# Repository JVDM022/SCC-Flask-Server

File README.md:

# scc-control-platform

A small SCADA-like research control platform for a thermal SCC/corrosion test rig. Arduino SCC firmware owns rig safety and fallback control, while an Intel NUC USB gateway handles communications to the Flask backend. PostgreSQL stores the time series, and the backend derives alarms, pump-cycle statistics, ML temperature predictions, and guarded MPC heater PWM recommendations. The React HMI dashboard provides live monitoring, trends, alarms, events, ML predictions, MPC output, firmware updates, and equipment health views.

## Architecture

```text
Arduino SCC controller -> USB serial -> Intel NUC gateway -> Flask API -> PostgreSQL
                                                                  |-> alarms and events
                                                                  |-> pump-cycle extraction
                                                                  |-> ML prediction
                                                                  |-> guarded MPC (opt-in)
                                                                  |-> React HMI dashboard
```

## Docker Setup

```bash
docker compose up --build
```

Backend: `http://localhost:5050`  
Frontend: `http://localhost:5173`

## Frontend HMI

The HMI is a React + Vite + TypeScript app in `frontend/hmi-dashboard`. It uses React Query for API polling, Plotly for dark engineering charts, and modular dashboard pages for operations, analytics, ML models, MPC, digital twin simulation, equipment health, event intelligence, and settings.

```bash
cd frontend/hmi-dashboard
npm install
npm run dev
```

## Live Telemetry

The default live path reads Arduino CSV telemetry over USB on the Intel NUC and posts parsed JSON to Flask:

```bash
cd backend
python -m app.services.nuc_gateway --serial-port /dev/ttyACM0 --api-base-url http://localhost:5000
```

Set `API_WRITE_KEY` in both the backend and gateway environment when write authentication is enabled. Common NUC gateway variables:

```text
NUC_SERIAL_PORT=/dev/ttyACM0
NUC_SERIAL_BAUD=115200
SCC_API_BASE_URL=http://localhost:5000
NUC_DEVICE_ID=intel-nuc-gateway
NUC_AVRDUDE_COMMAND=avrdude
NUC_ARDUINO_UPLOAD_BAUD=115200
```

Legacy ESP32 relay telemetry is still supported through MQTT. Devices publish JSON to:

```text
scc/site/<site_id>/rig/<rig_id>/device/<device_id>/telemetry
```

The Flask backend subscribes to Mosquitto when `MQTT_ENABLED=1`, parses MQTT payloads, stores telemetry, and derives alarms, pump-cycle records, ML predictions, and MPC recommendations.

## API Endpoints

- `GET /api/latest`: latest telemetry row.
- `GET /api/history?minutes=60`: telemetry history for plotting.
- `GET /api/events?limit=100`: pump and hard-kill events.
- `GET /api/alarms/active`: active alarms.
- `GET /api/pump-cycles`: extracted pump cycle statistics.
- `GET /api/ml/prediction`: predicted temperatures for +1s, +5s, and +10s when models exist.
- `GET /api/mpc/status`: closed-loop enablement, model horizons, watchdog, and latest command state.
- `GET /api/mpc/recommendation`: advisory heater PWM recommendation.
- `POST /api/control/setpoint`: store a desired setpoint command.
- `POST /api/control/power`: queue a controller on/off command through the Intel NUC gateway.
- `POST /api/telemetry`: JSON telemetry ingest used by the Intel NUC gateway and development tools.
- `POST /api/telemetry/csv`: development/manual CSV import, not the live ESP32 path.

## Telemetry Format

Live MQTT telemetry is JSON. The development CSV import endpoint accepts CSV with or without a header. Headerless rows are parsed using this exact order:

```text
event,ms,temp_c,adc,dtemp_c_per_s,setpoint_c,mode,heater_pwm,heating,heater_lockout,pump_enabled,pump_allowed,pump_on,motor_pwm,motor_on_ms,motor_period_ms,temp_before_pump_c,min_temp_after_pump_c,last_pump_drop_c,recovery_time_s,manual_kill,hard_kill,uptime_s
```

Example:

```text
0,123456,126.42,222,-0.1300,125.00,3,184,1,0,1,1,0,155,150,30000,127.20,124.80,2.40,18.50,0,0,300
```

Event codes: `0` normal sample, `1` pump start, `2` pump end, `3` pump recovered, `4` hard kill, `5` sensor fault.

## Safety Philosophy

Arduino firmware and hardware own hard safety. Flask, ML, MPC, and the Intel NUC gateway are never the only protection layer. Closed-loop MPC is disabled by default (`MPC_CLOSED_LOOP_ENABLED=0`). When enabled, it only sends PWM overrides in PID-hold mode with ten contiguous telemetry samples and a loaded 5-second model. The Arduino expires an override after 3.5 seconds and returns to local PID. Heater lockout, a target-plus-0.5 C ceiling, manual kill, sensor fault, the optional runtime limit, and hard kill remain local firmware overrides.

The continuous-operation build sets `ENABLE_RUNTIME_LIMIT=0`, so it does not force a shutdown after 96 hours. Set the flag to `1` to restore that behavior. Manual kill, ADC/thermistor fault detection, heater lockout, and the hard temperature kill remain active regardless of this setting. Arduino `millis()` telemetry wraps normally after approximately 49.7 days.

The trained model is observational, so the backend also enforces a physically directed recovery floor: at least PWM 184 when temperature is 2 C or more below setpoint, and at least PWM 128 when it is 0.5 C or more below setpoint. This prevents a reverse-causality artifact in the training data from selecting zero heat during recovery.

Before each pump cycle, the backend also probes the 5-second model with a simulated pump-start state. It combines the predicted drop with the last measured pump drop and calculates `preheat target = setpoint + drop`, capped by `MPC_PREHEAT_MAX_C`. The Arduino waits for this target before re-enabling the pump. Its compile-time `MPC_PREHEAT_LIMIT_Cx100`, lockout, and hard-kill thresholds remain independent limits; changing the validated safety envelope requires reviewing all of them together.

## Manual Emergency Control

The Arduino starts in a fail-safe OFF state. The Operations HMI queues `SET_ON 1` to enable both heater control and the pump timer, and `SET_ON 0` to turn both outputs off. `KILL 1` immediately latches the system OFF; after `KILL 0`, the operator must deliberately select Turn On again. Set `API_WRITE_KEY` on the backend and `VITE_API_WRITE_KEY` on the frontend to the same value when command authentication is enabled. The NUC gateway polls:

```text
/api/firmware/commands/next?device=nuc
```

Pending manual kill and setpoint commands are delivered through that endpoint before Arduino OTA commands. Existing ESP32 relay firmware can still poll with `device=esp32` for legacy deployments.

## Dependency Explanation

- Flask: API server
- SQLAlchemy: ORM
- PostgreSQL: database
- pandas/numpy: data processing
- scikit-learn: ML models
- joblib: model persistence
- matplotlib/plotly: visualization
- APScheduler: background jobs
- pytest: testing
- xgboost/lightgbm: advanced ML models

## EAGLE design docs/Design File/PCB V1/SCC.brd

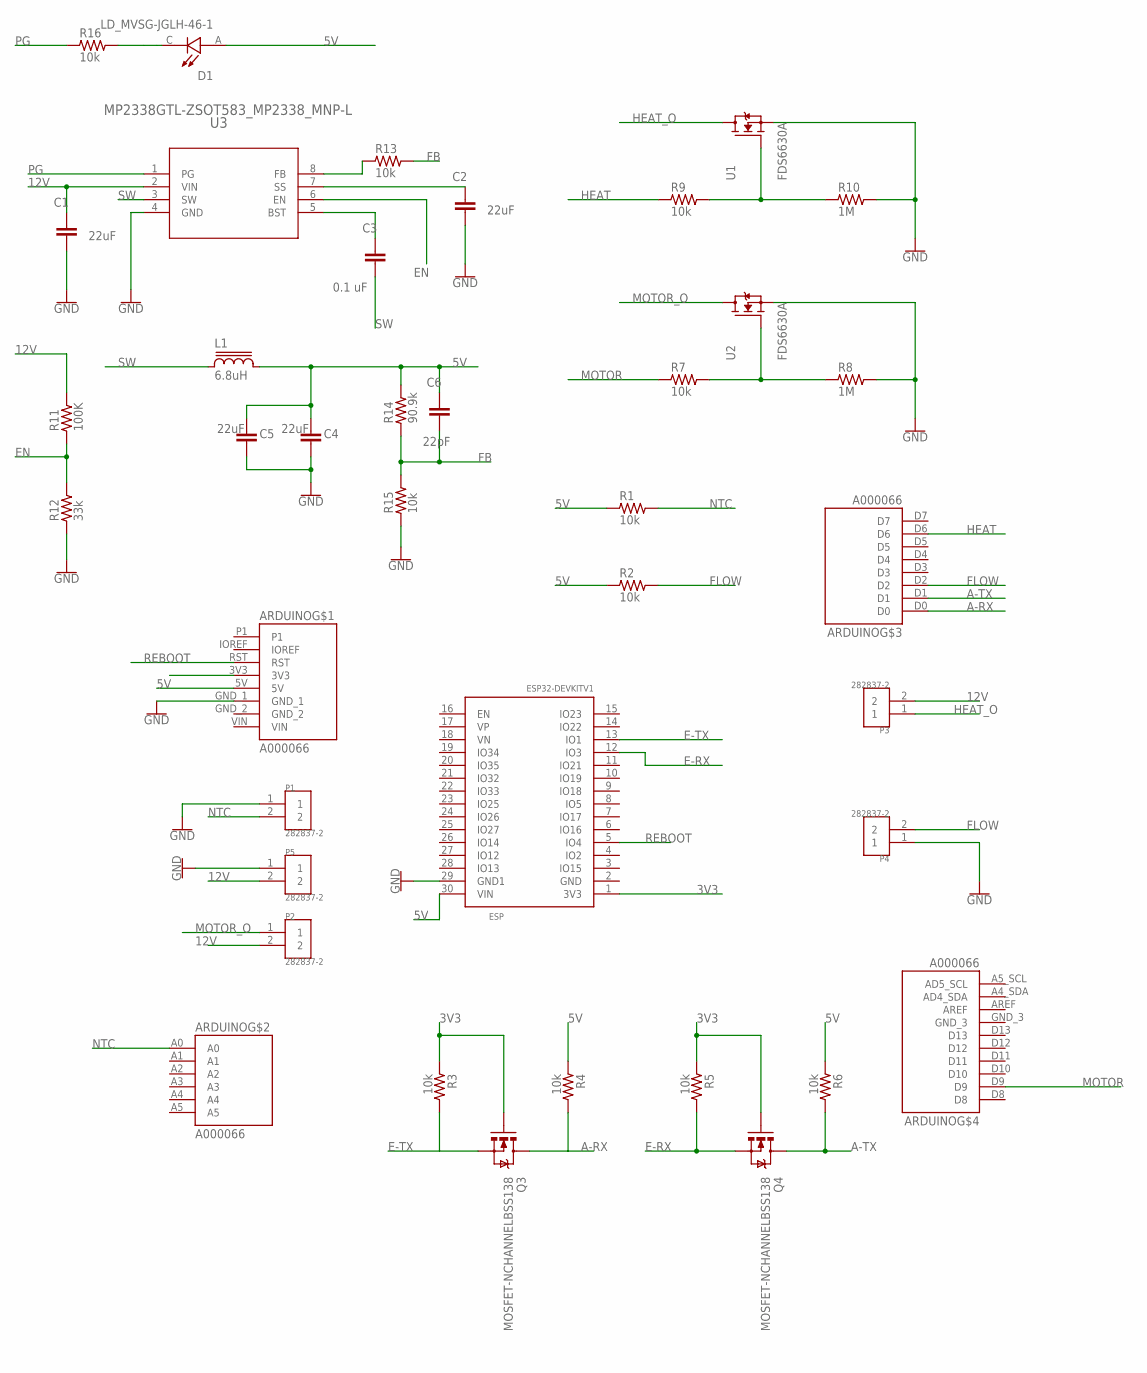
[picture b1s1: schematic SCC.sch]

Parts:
ARDUINO: A000066; ARDUINO_A000066
C1, C2, C4, C5: 22uF; CAP_1206
C3: 0.1 uF; CAP_0805
C6: 22pF; CAP_0805
D1: LD_MVSG-JGLH-46-1; LED_LD_MVSG-JGLH-46-1
ESP: ESP32DEVKITV1; ESP32-DEVKITV1
L1: 6.8uH; INDUCTOR-BOURNS_SRN8040
P1, P2, P3, P4, P5: 282837-2; TE_282837-2
Q3, Q4: MOSFET-NCHANNELBSS138; SOT23
R1, R2, R3, R4, R5, R6, R7, R9, R13, R15, R16: 10k; RC-MASTER-SMD_R0603MP
R8, R10: 1M; RC-MASTER-SMD_R0603MP
R11: 100K; RC-MASTER-SMD_R0603MP
R12: 33k; RC-MASTER-SMD_R0603MP
R14: 90.9k; RC-MASTER-SMD_R0603MP
U1, U2: FDS6630A; SOIC127P600X175-8N
U3: MP2338GTL-ZSOT583_MP2338_MNP-L; SOT583_MP2338_MNP-L

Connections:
3V3: ESP.1 (3V3), Q3.1 (G), Q4.1 (G), R3.1, R5.1
5V: ARDUINO.5V, C4.1, C5.1, C6.1, D1.A, ESP.30 (VIN), L1.2, R1.1, R2.1, R4.1, R6.1, R14.2
12V: C1.1, P2.2, P3.2, P5.2, R11.2, U3.2 (VIN)
A-RX: ARDUINO.D0, Q3.3 (D), R4.2
A-TX: ARDUINO.D1, Q4.3 (D), R6.2
E-RX: ESP.12 (IO3), Q4.2 (S), R5.2
E-TX: ESP.13 (IO1), Q3.2 (S), R3.2
EN: R11.1, R12.2, U3.6 (EN)
FB: C6.2, R13.2, R14.1, R15.2
FLOW: ARDUINO.D2, P4.2, R2.2
GND: ARDUINO.GND_1, C1.2, C2.2, C4.2, C5.2, ESP.29 (GND1), P1.1, P4.1, P5.1, R8.2, R10.2, R12.1, R15.1, U1.1 (S), U1.2 (S), U1.3 (S), U2.1 (S), U2.2 (S), U2.3 (S), U3.4 (GND)
GND_2: ARDUINO.GND_2
GND_3: ARDUINO.GND_3
HEAT: ARDUINO.D6, R9.1
HEAT_O: P3.1, U1.5 (D), U1.6 (D), U1.7 (D), U1.8 (D)
MOTOR: ARDUINO.D9, R7.1
MOTOR_O: P2.1, U2.5 (D), U2.6 (D), U2.7 (D), U2.8 (D)
unnamed: R7.2, R8.1, U2.4 (G)
unnamed: R9.2, R10.1, U1.4 (G)
unnamed: C3.1, U3.5 (BST)
unnamed: C2.1, U3.7 (SS)
unnamed: D1.C, R16.2
unnamed: R13.1, U3.8 (FB)
NTC: ARDUINO.A0, P1.2, R1.2
PG: R16.1, U3.1 (PG)
REBOOT: ARDUINO.RST, ESP.5 (IO4)
SW: C3.2, L1.1, U3.3 (SW)
VIN: ARDUINO.VIN

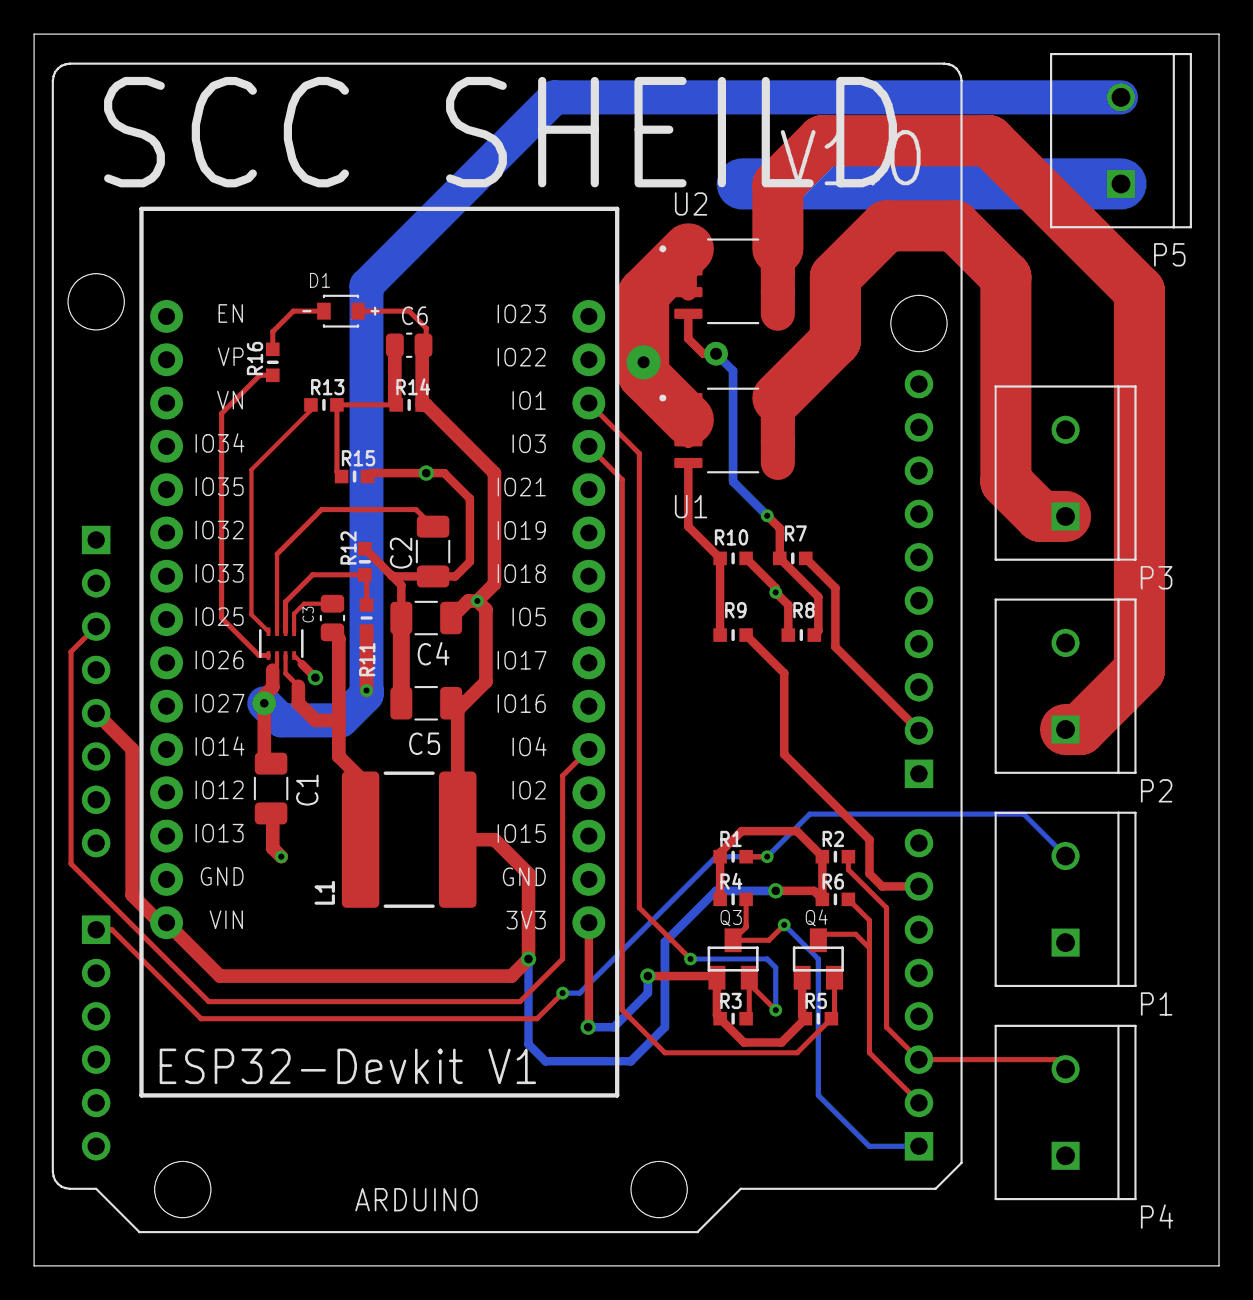
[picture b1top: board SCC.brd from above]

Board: 2 copper layers, 69.5 x 72.2 mm, 36 parts (0 on the bottom side), 25 nets.

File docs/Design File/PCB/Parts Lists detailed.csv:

"Part";"Value";"Device";"Package";"Description";"AVAILABILITY";"CHECK_PRICES";"COPYRIGHT";"CREATED_BY";"DATASHEET";"DESCRIPTION";"DIGIKEY_PART_NUMBER";"MANUFACTURER";"MANUFACTURER_NAME";"MANUFACTURER_PART_NUMBER";"MAXIMUM_PACKAGE_HEIGHT";"MF";"MP";"MPN";"PACKAGE";"PARTREV";"PRICE";"PROD_ID";"PURCHASE-URL";"SNAPEDA_LINK";"STANDARD";
"ARDUINO";"A000066";"A000066";"ARDUINO_A000066";"Check availability";"In Stock";"https://www.snapeda.com/parts/A000066/Arduino/view-part/?ref=eda";"";"";"";"                                                      Arduino UNO Rev3 Microcontroller Board, ATmega328P | Arduino A000066                                              ";"";"";"";"";"";"Arduino";"A000066";"";"Non-Standard Arduino";"";"None";"";"https://www.snapeda.com/api/url_track_click_mouser/?unipart_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 uno r3";"https://www.snapeda.com/parts/A000066/Arduino/view-part/?ref=snap";"";
"C1";"22uF";"GRM31CR60J107ME39L";"CAP_1206";"CAP CER 100UF 6.3V X5R 1206";"";"";"";"PCBLayout.com";"";"";"GRM31CR60J107ME39L";"Murata Electronics North America";"";"";"";"";"";"GRM31CR60J107ME39L";"SMD 1206";"";"";"";"";"";"";
"C2";"22uF";"GRM31CR60J107ME39L";"CAP_1206";"CAP CER 100UF 6.3V X5R 1206";"";"";"";"PCBLayout.com";"";"";"GRM31CR60J107ME39L";"Murata Electronics North America";"";"";"";"";"";"GRM31CR60J107ME39L";"SMD 1206";"";"";"";"";"";"";
"C3";"0.1 uF";"CC0805KRX7R9BB104";"CAP_0805";"CAP CER 0.1UF 50V X7R 0805";"";"";"";"PCBLayout.com";"";"";"311-1140-2-ND";"Yageo";"";"";"";"";"";"CC0805KRX7R9BB104";"SMD 0805";"";"";"";"";"";"";
"C4";"22uF";"GRM31CR60J107ME39L";"CAP_1206";"CAP CER 100UF 6.3V X5R 1206";"";"";"";"PCBLayout.com";"";"";"GRM31CR60J107ME39L";"Murata Electronics North America";"";"";"";"";"";"GRM31CR60J107ME39L";"SMD 1206";"";"";"";"";"";"";
"C5";"22uF";"GRM31CR60J107ME39L";"CAP_1206";"CAP CER 100UF 6.3V X5R 1206";"";"";"";"PCBLayout.com";"";"";"GRM31CR60J107ME39L";"Murata Electronics North America";"";"";"";"";"";"GRM31CR60J107ME39L";"SMD 1206";"";"";"";"";"";"";
"ESP";"ESP32DEVKITV1";"ESP32DEVKITV1";"ESP32-DEVKITV1";"";"";"";"";"";"";"";"";"";"";"";"";"";"";"";"";"";"";"";"";"";"";
"L1";"6.8uH";"INDUCTOR-BOURNS_SRN8040";"INDUCTOR-BOURNS_SRN8040";"POWER INDUCTOR";"";"";"";"";"";"";"";"";"";"";"";"";"";"";"";"";"";"";"";"";"";
"P1";"282837-2";"282837-2";"TE_282837-2";"";"Good";"";"";"";"";"TERMINAL BLOCK 3.5MM 2POS PCB";"";"";"";"";"";"On Shore";"OSTTE020104";"";"None";"G3";"0.28 USD";"";"";"";"";
"P2";"282837-2";"282837-2";"TE_282837-2";"";"Good";"";"";"";"";"TERMINAL BLOCK 3.5MM 2POS PCB";"";"";"";"";"";"On Shore";"OSTTE020104";"";"None";"G3";"0.28 USD";"";"";"";"";
"P3";"282837-2";"282837-2";"TE_282837-2";"";"Good";"";"";"";"";"TERMINAL BLOCK 3.5MM 2POS PCB";"";"";"";"";"";"On Shore";"OSTTE020104";"";"None";"G3";"0.28 USD";"";"";"";"";
"P4";"282837-2";"282837-2";"TE_282837-2";"";"Good";"";"";"";"";"TERMINAL BLOCK 3.5MM 2POS PCB";"";"";"";"";"";"On Shore";"OSTTE020104";"";"None";"G3";"0.28 USD";"";"";"";"";
"P5";"282837-2";"282837-2";"TE_282837-2";"";"Good";"";"";"";"";"TERMINAL BLOCK 3.5MM 2POS PCB";"";"";"";"";"";"On Shore";"OSTTE020104";"";"None";"G3";"0.28 USD";"";"";"";"";
"Q3";"MOSFET-NCHANNELBSS138";"MOSFET-NCHANNELBSS138";"SOT23";"Common NMOSFET Parts";"";"";"";"";"";"";"";"";"";"";"";"";"";"";"";"";"";"TRANS-00830";"";"";"";
"Q4";"MOSFET-NCHANNELBSS138";"MOSFET-NCHANNELBSS138";"SOT23";"Common NMOSFET Parts";"";"";"";"";"";"";"";"";"";"";"";"";"";"";"";"";"";"TRANS-00830";"";"";"";
"R1";"10k";"RC-MASTER-SMD_R_0603MP";"RC-MASTER-SMD_R0603MP";"RESISTOR";"";"";"";"";"";"";"";"";"";"";"";"";"";"";"";"";"";"";"";"";"";
"R2";"10k";"RC-MASTER-SMD_R_0603MP";"RC-MASTER-SMD_R0603MP";"RESISTOR";"";"";"";"";"";"";"";"";"";"";"";"";"";"";"";"";"";"";"";"";"";
"R3";"10k";"RC-MASTER-SMD_R_0603MP";"RC-MASTER-SMD_R0603MP";"RESISTOR";"";"";"";"";"";"";"";"";"";"";"";"";"";"";"";"";"";"";"";"";"";
"R4";"10k";"RC-MASTER-SMD_R_0603MP";"RC-MASTER-SMD_R0603MP";"RESISTOR";"";"";"";"";"";"";"";"";"";"";"";"";"";"";"";"";"";"";"";"";"";
"R5";"10k";"RC-MASTER-SMD_R_0603MP";"RC-MASTER-SMD_R0603MP";"RESISTOR";"";"";"";"";"";"";"";"";"";"";"";"";"";"";"";"";"";"";"";"";"";
"R6";"10k";"RC-MASTER-SMD_R_0603MP";"RC-MASTER-SMD_R0603MP";"RESISTOR";"";"";"";"";"";"";"";"";"";"";"";"";"";"";"";"";"";"";"";"";"";
"R7";"10k";"RC-MASTER-SMD_R_0603MP";"RC-MASTER-SMD_R0603MP";"RESISTOR";"";"";"";"";"";"";"";"";"";"";"";"";"";"";"";"";"";"";"";"";"";
"R8";"1M";"RC-MASTER-SMD_R_0603MP";"RC-MASTER-SMD_R0603MP";"RESISTOR";"";"";"";"";"";"";"";"";"";"";"";"";"";"";"";"";"";"";"";"";"";
"R9";"10k";"RC-MASTER-SMD_R_0603MP";"RC-MASTER-SMD_R0603MP";"RESISTOR";"";"";"";"";"";"";"";"";"";"";"";"";"";"";"";"";"";"";"";"";"";
"R10";"1M";"RC-MASTER-SMD_R_0603MP";"RC-MASTER-SMD_R0603MP";"RESISTOR";"";"";"";"";"";"";"";"";"";"";"";"";"";"";"";"";"";"";"";"";"";
"R11";"100K";"RC-MASTER-SMD_R_0603MP";"RC-MASTER-SMD_R0603MP";"RESISTOR";"";"";"";"";"";"";"";"";"";"";"";"";"";"";"";"";"";"";"";"";"";
"R12";"33k";"RC-MASTER-SMD_R_0603MP";"RC-MASTER-SMD_R0603MP";"RESISTOR";"";"";"";"";"";"";"";"";"";"";"";"";"";"";"";"";"";"";"";"";"";
"R13";"10k";"RC-MASTER-SMD_R_0603MP";"RC-MASTER-SMD_R0603MP";"RESISTOR";"";"";"";"";"";"";"";"";"";"";"";"";"";"";"";"";"";"";"";"";"";
"R14";"90.9k";"RC-MASTER-SMD_R_0603MP";"RC-MASTER-SMD_R0603MP";"RESISTOR";"";"";"";"";"";"";"";"";"";"";"";"";"";"";"";"";"";"";"";"";"";
"R15";"10k";"RC-MASTER-SMD_R_0603MP";"RC-MASTER-SMD_R0603MP";"RESISTOR";"";"";"";"";"";"";"";"";"";"";"";"";"";"";"";"";"";"";"";"";"";
"U1";"FDS6630A";"FDS6630A";"SOIC127P600X175-8N";"";"";"";"";"";"";"";"";"ON SEMICONDUCTOR";"";"";"1.75 mm";"";"";"";"";"C1";"";"";"";"";"IPC 7351B";
"U2";"FDS6630A";"FDS6630A";"SOIC127P600X175-8N";"";"";"";"";"";"";"";"";"ON SEMICONDUCTOR";"";"";"1.75 mm";"";"";"";"";"C1";"";"";"";"";"IPC 7351B";
"U3";"MP2338GTL-ZSOT583_MP2338_MNP-L";"MP2338GTL-ZSOT583_MP2338_MNP-L";"SOT583_MP2338_MNP-L";"";"";"";"Copyright (C) 2026 Ultra Librarian. All rights reserved.";"";"https://www.monolithicpower.com/en/documentview/productdocum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";"High-Efficiency 28V 3A 450kHz Synchronous Step-Down Converter In SOT583 Package";"";"";"Monolithic Power Systems";"MP2338GTL-Z";"";"";"";"";"";"";"";"";"";"";"";

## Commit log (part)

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2026-06-04 Initial SCC control platform V0.1
2026-06-04 V0.1.1 - Initial OTA features for both arduino and ESP32
2026-06-06 SCC cotnrol platform V0.1.1 - Add Cloudflare tunnel deployment
2026-06-06 SCC control V0.1.1 - Allow Cloudflare app hostname in Vite
2026-06-06 SCC control V0.1.1.2 - Add extra hosts configuration
2026-06-06 SCC control V0.1.1.3 - Add API key protection for write endpoints
2026-06-08 SCC control V0.1.1.4 - modified ESP32 Relay firmware to use MQTT instead of IoT Hub - Updated WiFi credentials header to include MQTT broker configuration. - Removed IoT Hub related definitions and f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
2026-06-12 SCC control V0.1.1.4 - Add diagrams to documentations
2026-06-12 SCC control V0.1.1.5 - Added Heater Testing, Telemetry Testing (Relay and Parsing), NTC Testing, Motor Testing
2026-06-12 V0.1.1.5 - added alerts, manual kill
2026-06-15 SCC control V0.1.1.5 - Added comprehensive safety, deployment, operation, troubleshooting, and verification guides
2026-06-15 SCC control V0.1.1.5 - Refactored telemetry configuration checks to ensure API key is optional
2026-06-16 Enhance telemetry handling and Wi-Fi configuration in ESP32 firmware
2026-06-17 SCC control V0.1.1.6: feat: Add setpoint command handling in firmware and update tests
    - Implemented a new "SETPOINT" command in the firmware to allow dynamic setpoint adjustments.
    - Updated the main control logic to handle the new command and provide appropriate feedback.
    - Enhanced unit tests to cover scenarios for setting and rejecting out-of-band setpoints.
    - Modified existing tests to align with the new target setpoint variable.
    - Updated the HMI dashboard to reflect changes in firmware interactions, including updated messaging for Arduino and ESP32.
    - Removed obsolete ESP32 testing files and configurations as the focus shifts to Arduino.
2026-06-17 SCC control V0.1.1.6: Remove obsolete files and code from ESP32-Relay firmware
    - Deleted autogenerated CMakeLists.txt as it is no longer needed.
    - Removed main.c file containing the core application logic, as it has been replaced or is no longer in use.
    - Cleared test directory and associated test files, including README and test_relay_core.c, to streamline the project structure.
    - Deleted README.md file that provided outdated information about the ESP32 firmware project.
2026-06-17 SCC control V0.1.1.6: Add new documentation files for SCC setup and TDM
    - Added "SCC setup photo.JPG" to provide a visual reference for SCC setup.
    - Included "SCC 316 TDM.docx" as a new document for TDM-related information.
    - Added temporary file "~$C 316 TDM.docx" which appears to be a lock file for the document.
2026-06-18 Update telemetry pipeline documentation and mock telemetry implementation
2026-06-21 SCC control V0.1.1.6: Update target temperature and heater thresholds in Arduino heater testing firmware

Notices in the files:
parts and their libraries:
COPYRIGHT: Copyright (C) 2026 Ultra Librarian. All rights reserved.
SparkFun-PowerSymbols: Licensing: Creative Commons ShareAlike 4.0 International - https://creativecommons.org/licenses/by-sa/4.0
